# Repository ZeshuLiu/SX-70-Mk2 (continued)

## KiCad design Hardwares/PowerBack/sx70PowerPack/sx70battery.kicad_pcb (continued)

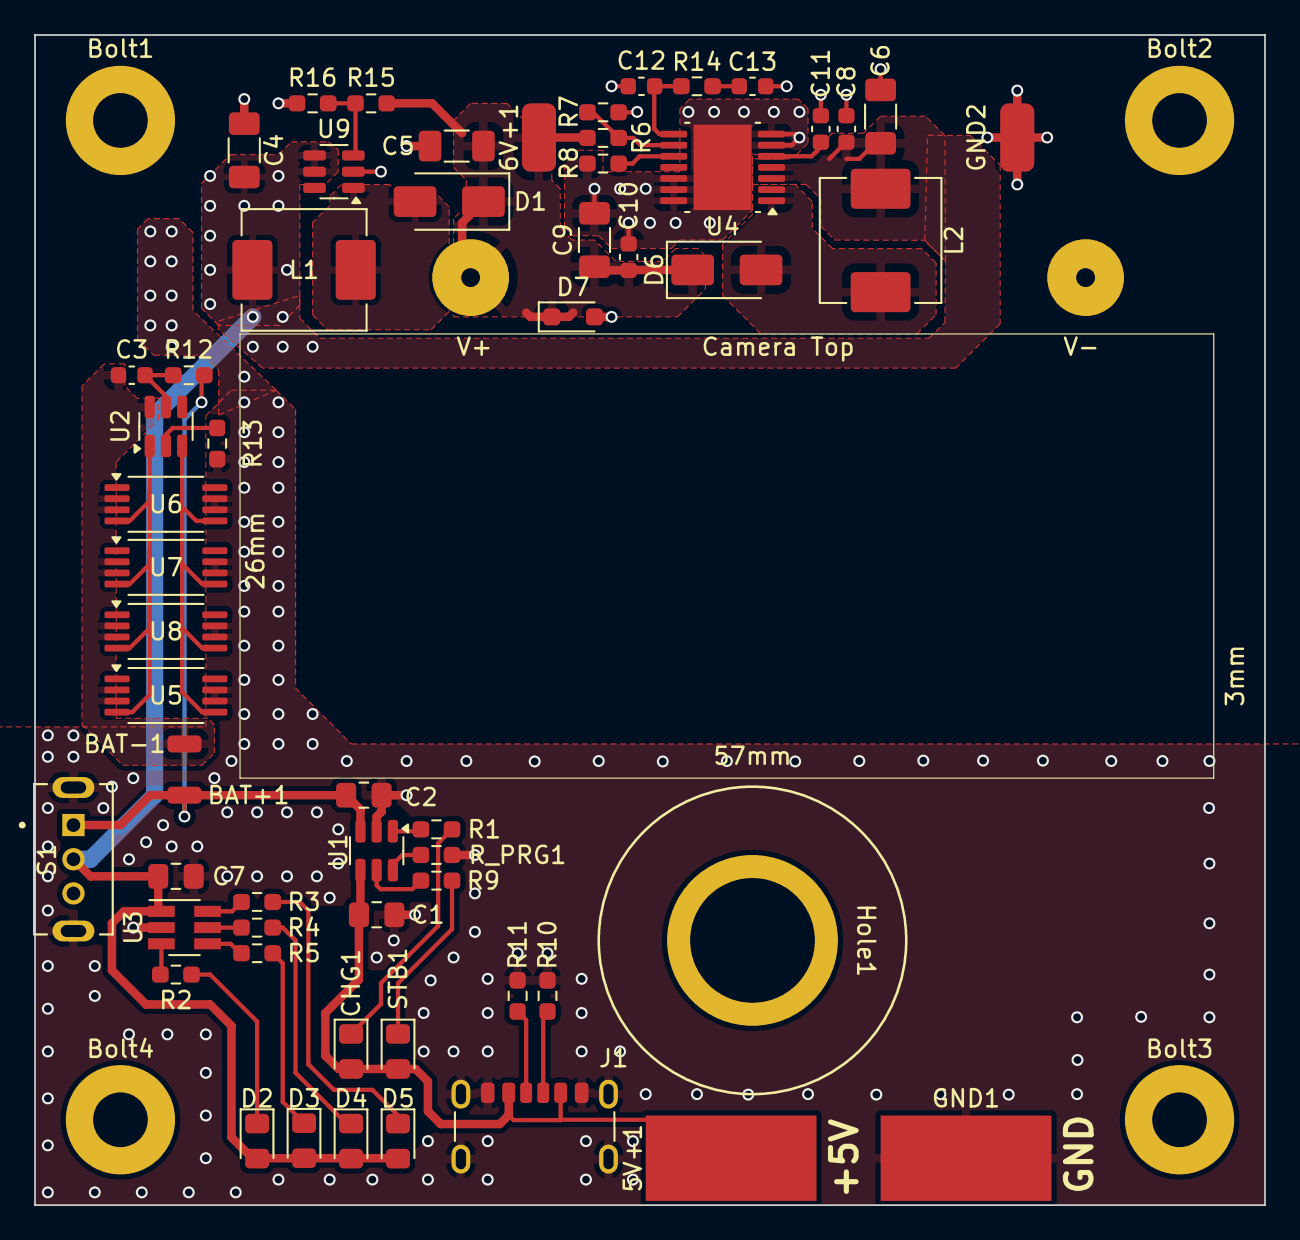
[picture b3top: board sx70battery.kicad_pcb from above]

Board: 2 copper layers, 72.0 x 68.5 mm, 64 parts (0 on the bottom side), 33 nets.

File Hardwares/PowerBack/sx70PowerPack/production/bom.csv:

Designator,Footprint,Quantity,Value,LCSC Part #
5V+1,SolderWirePad_1x01_SMD_5x10mm,1,5V+,
6V+1,SolderWirePad_1x01_SMD_1x2mm,1,6V+,
BAT+1,SolderWirePad_1x01_SMD_1x2mm,1,BAT+,
BAT-1,SolderWirePad_1x01_SMD_1x2mm,1,BAT-,
"BOLT1, BOLT2, BOLT3, BOLT4",MountingHole_3.2mm_M3_Pad,4,M3_BOLT,
C1,0805,1,4.7uf,
C10,0603,1,1uf,
C11,0603,1,22nf,
C12,0603,1,2nf,
"C13, C3, C8",0603,3,100nf,
C2,0805,1,10u,
C4,1206,1,1uf,
C5,1206,1,10uf,
C6,1206,1,22uf,
C7,0805,1,1u,
C9,1206,1,47uf,
"CHG1, D2, D3, D4, D5, STB1",0805,6,LED,
"D1, D6",D_SMA,2,SS34,
D7,D_SOD-323_HandSoldering,1,1N5819WS,
GND1,SolderWirePad_1x01_SMD_5x10mm,1,GND,
GND2,SolderWirePad_1x01_SMD_1x2mm,1,GND,
HOLE1,Tripod_hole,1,Tripod_hole,
J1,USB_C_Receptacle_GCT_USB4125-xx-x-0190_6P_TopMnt_Horizontal,1,USB_C_Receptacle_PowerOnly_6P,
L1,L_APV_APH0650,1,4.7uH,
L2,L_APV_APH0650,1,3.3uH,
"R1, R13, R9",0603,3,1k,
"R10, R11",0603,2,5.1k,
R12,0603,1,100,
R14,0603,1,866,
R15,0603,1,330k,
R16,0603,1,51k,
"R2, R3, R4, R5",0603,4,3.3k,
R6,0603,1,39k,
"R7, R_PRG1",0603,2,10k,
R8,0603,1,60.4k,
S1,SW_SS12D07VG4,1,SS12D07VG4,
SX70_POGOPIN1,sx_70_pogopin_phi2mm,1,Sx70_Pogopin,
U1,SOT-23-6,1,TP4057,
U2,SOT-23-6,1,DW01A,
U3,SOT-23-6_Handsoldering,1,LN60A,
U4,HTSSOP-14-1EP_4.4x5mm_P0.65mm_EP3.4x5mm_Mask3x3.1mm,1,~,
"U5, U6, U7, U8",TSSOP-8_4.4x3mm_P0.65mm,4,~,
U9,SOT-23-6,1,TLV61048DBVR,

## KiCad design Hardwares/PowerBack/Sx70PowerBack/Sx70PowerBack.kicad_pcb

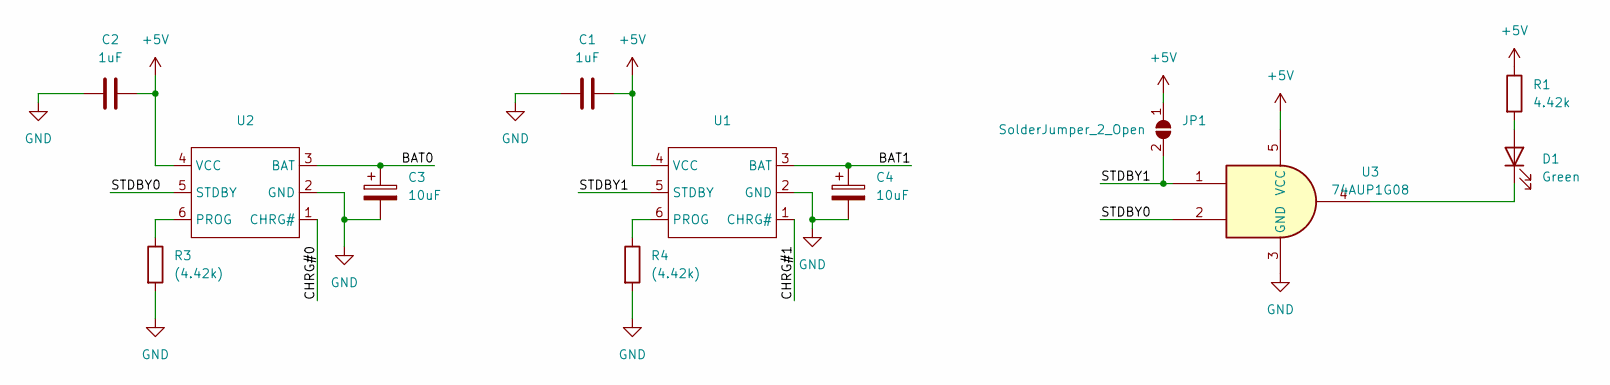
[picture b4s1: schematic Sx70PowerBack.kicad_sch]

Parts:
C1, C2: 1uF; C_0805_2012Metric_Pad1.18x1.45mm_HandSolder
C3, C4: 10uF; CP_EIA-3528-21_Kemet-B_Pad1.50x2.35mm_HandSolder
D1: Green; LED_0805_2012Metric_Pad1.15x1.40mm_HandSolder
JP1: SolderJumper_2_Open; SolderJumper-2_P1.3mm_Open_TrianglePad1.0x1.5mm
R1: 4.42k; R_0603_1608Metric_Pad0.98x0.95mm_HandSolder
R3, R4: (4.42k); R_0603_1608Metric_Pad0.98x0.95mm_HandSolder
U1, U2: SOT-23-6
U3: 74AUP1G08; Texas_R-PDSO-G5_DCK-5

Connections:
+5V: C1.2, C2.2, JP1.1 (A), R1.1, U1.4 (VCC), U2.4 (VCC), U3.5 (VCC)
/BAT0: C3.1, U2.3 (BAT)
/BAT1: C4.1, U1.3 (BAT)
/CHRG#0: U2.1 (CHRG#)
/CHRG#1: U1.1 (CHRG#)
/STDBY0: U2.5 (STDBY), U3.2
/STDBY1: JP1.2 (B), U1.5 (STDBY), U3.1
GND: C1.1, C2.1, C3.2, C4.2, R3.2, R4.2, U1.2 (GND), U2.2 (GND), U3.3 (GND)
unnamed: D1.2 (A), R1.2
unnamed: D1.1 (K), U3.4
unnamed: R4.1, U1.6 (PROG)
unnamed: R3.1, U2.6 (PROG)

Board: 2 copper layers, 12 parts (0 on the bottom side), 10 nets, no tracks yet.

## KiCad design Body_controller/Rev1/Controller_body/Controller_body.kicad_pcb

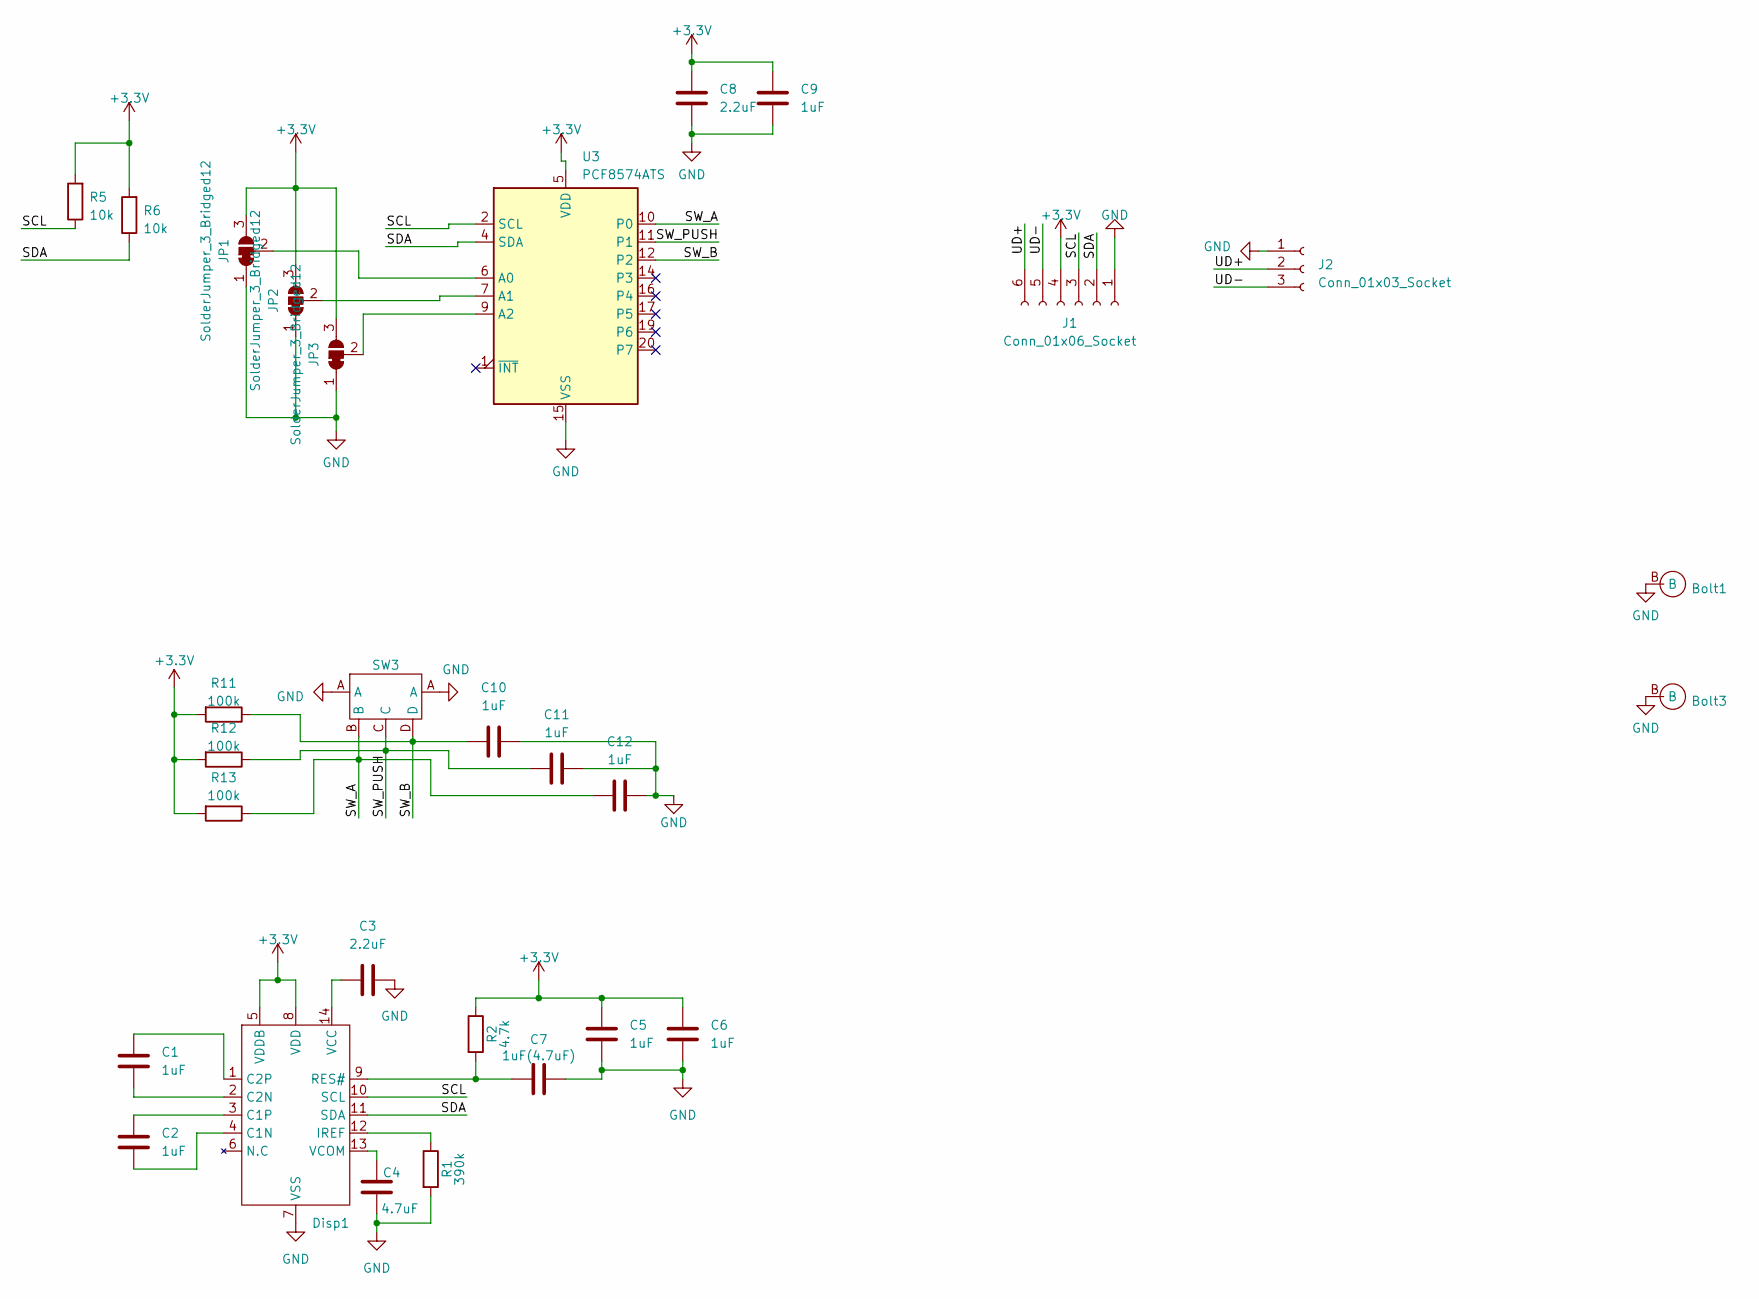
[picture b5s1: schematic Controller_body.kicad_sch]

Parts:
Bolt1, Bolt3: M3_Bolt
C1, C2, C5, C6, C9, C10, C11, C12: 1uF; C_0603_1608Metric_Pad1.08x0.95mm_HandSolder
C3, C8: 2.2uF; C_0603_1608Metric_Pad1.08x0.95mm_HandSolder
C4: 4.7uF; C_0603_1608Metric_Pad1.08x0.95mm_HandSolder
C7: 1uF(4.7uF); C_0603_1608Metric_Pad1.08x0.95mm_HandSolder
Disp1: SSD1306_0.91_i2c
J1: Conn_01x06_Socket; TE_84953-6_1x06-1MP_P1.0mm_Horizontal
J2: Conn_01x03_Socket; PinHeader_1x03_P2.54mm_Horizontal
JP1, JP2, JP3: SolderJumper_3_Bridged12; SolderJumper-3_P1.3mm_Bridged12_RoundedPad1.0x1.5mm_NumberL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
R1: 390k; R_0603_1608Metric_Pad0.98x0.95mm_HandSolder
R2: 4.7k; R_0603_1608Metric_Pad0.98x0.95mm_HandSolder
R5, R6: 10k; R_0805_2012Metric_Pad1.20x1.40mm_HandSolder
R11, R12, R13: 100k; R_0603_1608Metric_Pad0.98x0.95mm_HandSolder
SW3: Direction3 Pin5
U3: PCF8574ATS; SSOP-20_4.4x6.5mm_P0.65mm

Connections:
+3.3V: C5.1, C6.1, C8.1, C9.1, Disp1.5 (VDDB), Disp1.8 (VDD), J1.4, JP1.3 (B), JP2.3 (B), JP3.3 (B), R2.1, R5.2, R6.2, R11.2, R12.2, R13.2, U3.5 (VDD)
/SCL: Disp1.10 (SCL), J1.3, R5.1, U3.2 (SCL)
/SDA: Disp1.11 (SDA), J1.2, R6.1, U3.4 (SDA)
/SW_A: C12.1, R13.1, SW3.B, U3.10 (P0)
/SW_B: C10.1, R11.1, SW3.D, U3.12 (P2)
/SW_PUSH: C11.1, R12.1, SW3.C, U3.11 (P1)
/UD+: J1.6, J2.2
/UD-: J1.5, J2.3
GND: Bolt1.B, Bolt3.B, C3.2, C4.1, C5.2, C6.2, C7.2, C8.2, C9.2, C10.2, C11.2, C12.2, Disp1.7 (VSS), J1.1, J2.1, JP1.1 (A), JP2.1 (A), JP3.1 (A), R1.2, SW3.A, U3.15 (VSS)
unnamed: C2.2, Disp1.4 (C1N)
unnamed: C2.1, Disp1.3 (C1P)
unnamed: C1.2, Disp1.2 (C2N)
unnamed: C1.1, Disp1.1 (C2P)
unnamed: Disp1.12 (IREF), R1.1
unnamed: C7.1, Disp1.9 (RES#), R2.2
unnamed: C3.1, Disp1.14 (VCC)
unnamed: C4.2, Disp1.13 (VCOM)
unnamed: JP1.2 (C), U3.6 (A0)
unnamed: JP2.2 (C), U3.7 (A1)
unnamed: JP3.2 (C), U3.9 (A2)

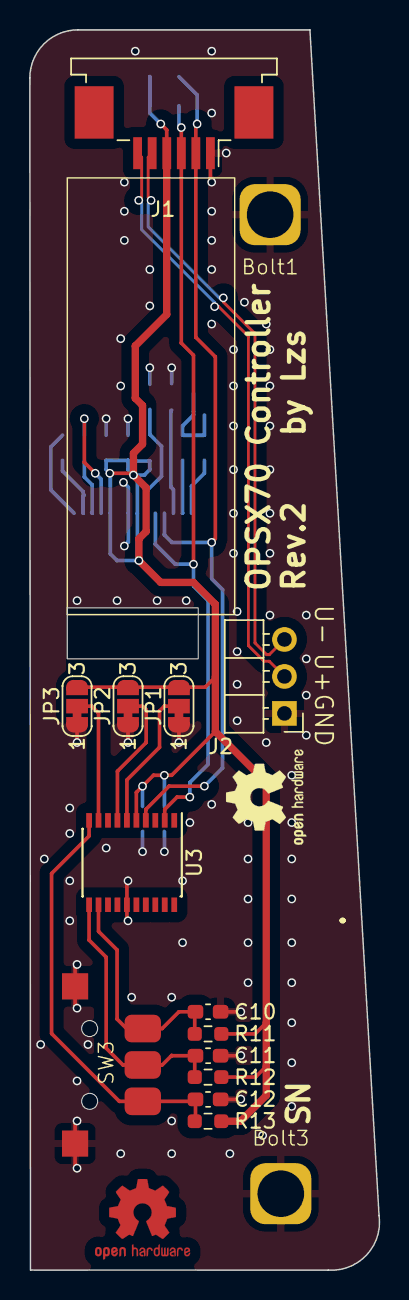
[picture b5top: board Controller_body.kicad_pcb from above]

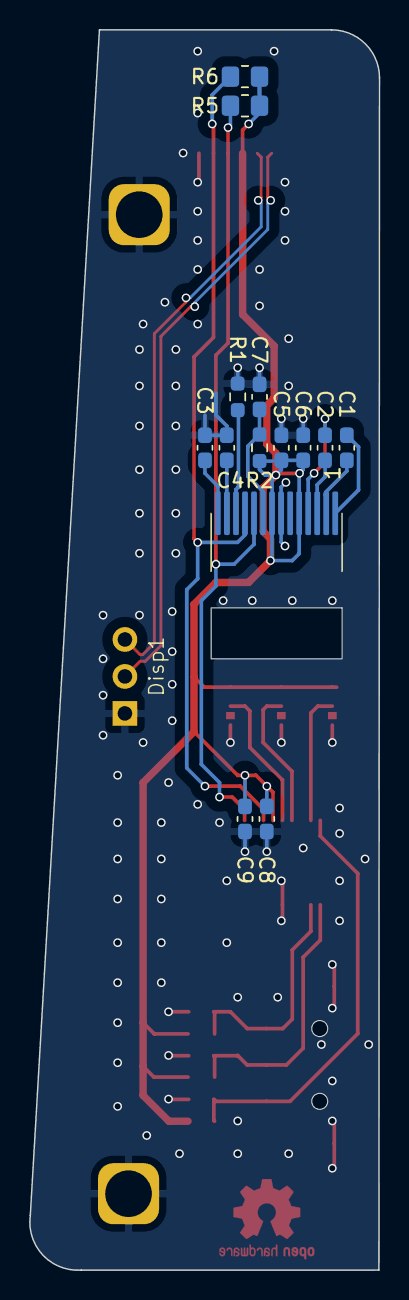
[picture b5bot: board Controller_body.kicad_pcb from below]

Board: 2 copper layers, 24.0 x 85.2 mm, 29 parts (14 on the bottom side), 20 nets.

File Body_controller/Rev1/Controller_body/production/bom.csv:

Designator,Footprint,Quantity,Value,LCSC Part #
"Bolt1, Bolt3",M3_Bolt,2,~,
"C1, C10, C11, C12, C2, C5, C6, C9",0603,8,1uF,
"C3, C8",0603,2,2.2uF,
C4,0603,1,4.7uF,
C7,0603,1,1uF(4.7uF),
Disp1,SSD1306_0.91_i2c,1,~,
J1,TE_84953-6_1x06-1MP_P1.0mm_Horizontal,1,Conn_01x06_Socket,
J2,PinHeader_1x03_P2.54mm_Horizontal,1,Conn_01x03_Socket,
"JP1, JP2, JP3",SolderJumper-3_P1.3mm_Bridged12_RoundedPad1.0x1.5mm_NumberLabels,3,SolderJumper_3_Bridged12,
R1,0603,1,390k,
"R11, R12, R13",0603,3,100k,
R2,0603,1,4.7k,
"R5, R6",0805,2,10k,
SW3,Direction3 Pin5,1,~,
U3,SSOP-20_4.4x6.5mm_P0.65mm,1,PCF8574ATS,

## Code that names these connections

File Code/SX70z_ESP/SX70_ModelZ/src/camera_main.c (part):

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
// S1 按键去抖计数
#define S1_DEBOUNCE_COUNT 5
static uint8_t s1f = 0;
static uint8_t s1t = 0;

static void debounce_read_s1pin(void)
{
    if (gpio_get_level(S1T_PIN) == 0) {
        s1t = (s1t == 0) ? s1t : s1t - 1;
    } else {
        s1t = S1_DEBOUNCE_COUNT;
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        char mode = camera_state.shut_mode;

        // 关闭 LED
        gpio_set_level(LED1_PIN, 1);

        // ---- 1. 关闭快门 ----
        ESP_LOGD(TAG, "Shutter close");
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        ESP_LOGD(TAG, "Shutter closed");

        // ---- 2. 电机启动，反光板上升 ----
        gpio_set_level(MOTOR_PIN, 1);
        ESP_LOGI(TAG, "Motor start (mirror up)");

        // 等待反光板就位 (S3 变高, 5×7µs 防抖)
        while (!gpio_debounce_defaultLow(S3_PIN)) {
            delay_us(100);
        }
        gpio_set_level(MOTOR_PIN, 0);
        ESP_LOGI(TAG, "Motor stopped");

        // ---- 3. Y Delay ----
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            delay_us(15000);              // 15ms

            // 等待 S1T 释放
            while (gpio_get_level(S1T_PIN) == 0) {
                delay_us(3000);
            }

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            sol1_release();               // shutter_open

            // 等待 S1T 释放
            while (gpio_get_level(S1T_PIN) == 0) {
                delay_us(100);
            }
            // 等待 S1T 再次按下
            while (gpio_get_level(S1T_PIN) != 0) {
                delay_us(3000);
            }
        }
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        }

        // ---- 7. 电机启动吐片 ----
        gpio_set_level(MOTOR_PIN, 1);
        ESP_LOGI(TAG, "Motor start (film ejection)");

        // 等待 S5 变低（胶片检测, 5×7µs 防抖）
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            delay_us(100);
        }

        gpio_set_level(MOTOR_PIN, 0);
        sol1_release();               // shutter_open
        ESP_LOGI(TAG, "Film ejection complete");

        // ---- 8. 等待 S1T 释放，防止连拍 ----
        while (gpio_get_level(S1T_PIN) == 0) {
            delay_us(10000);  // 10ms
        }
    }
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        // 无屏幕时 LED 心跳指示，有屏幕则保持熄灭
        if (!camera_state.if_display) {
            camera_state.test_led_level = !camera_state.test_led_level;
            gpio_set_level(LED1_PIN, camera_state.test_led_level);
        } else {
            gpio_set_level(LED1_PIN, 1);  // LED 低电平点亮，1=灭
        }
        vTaskDelay(pdMS_TO_TICKS(100));
    }
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
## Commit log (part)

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2023-06-03 Initial_Commit
2023-06-04 LT mode start
2023-08-20 Some photos
2023-08-20 Create LICENSE
2023-09-10 手动设置曝光时间从 1/1000 - 4分钟
2023-09-12 Save Cal File
2023-09-12 Ver 1.0
2023-09-12 Ver 1.0.1
2023-09-15 Stop Maintanience
2024-03-06 定时器高精度控制快门
2024-03-07 基本上可用
2024-03-07 新的手动控制方式
2024-03-08 可以正常工作（使用3维按钮）
2024-03-14 初步校准快门速度，现在呈现步进状态
2024-03-17 修复不闪光错误、完成空机测试，准备开始相纸测试
2024-03-18 实验调整了快门速度
2024-03-18 修复若干BUG
2024-03-19 update camera_driver
2024-03-19 快门速度基本OK + 外壳基本OK
2024-03-31 自拍定时OK
2024-04-09 整理代码及Readme
2024-04-09 更新Readme
2024-09-09 重新整理仓库
2024-09-09 外置电池设计
2024-09-10 外置电池设计完毕，生成光绘文件
2024-09-11 电池2.1版本（CC识别可以充电）
2026-04-12 C版本PCF8575能用
2026-04-12 显示功能已经具备，开机烧录功能也OK
2026-04-12 外围设备ok，相机功能准备开发
2026-04-12 对焦部分测试OK
2026-04-12 基本功能移植完毕
2026-04-12 闪光灯可以缩光圈；快门工作时还存在LED灯亮着的问题，尝试修复但为成果
2026-04-18 代码OK，电屁股正在做
2026-04-26 声纳工作正常
2026-04-26 增加防抖，防止机身动作不到位
2026-04-26 增加故障诊断
2026-05-10 修改SX70zPCB的小问题，投产机身控制器
2026-05-31 闪光灯速度限制
